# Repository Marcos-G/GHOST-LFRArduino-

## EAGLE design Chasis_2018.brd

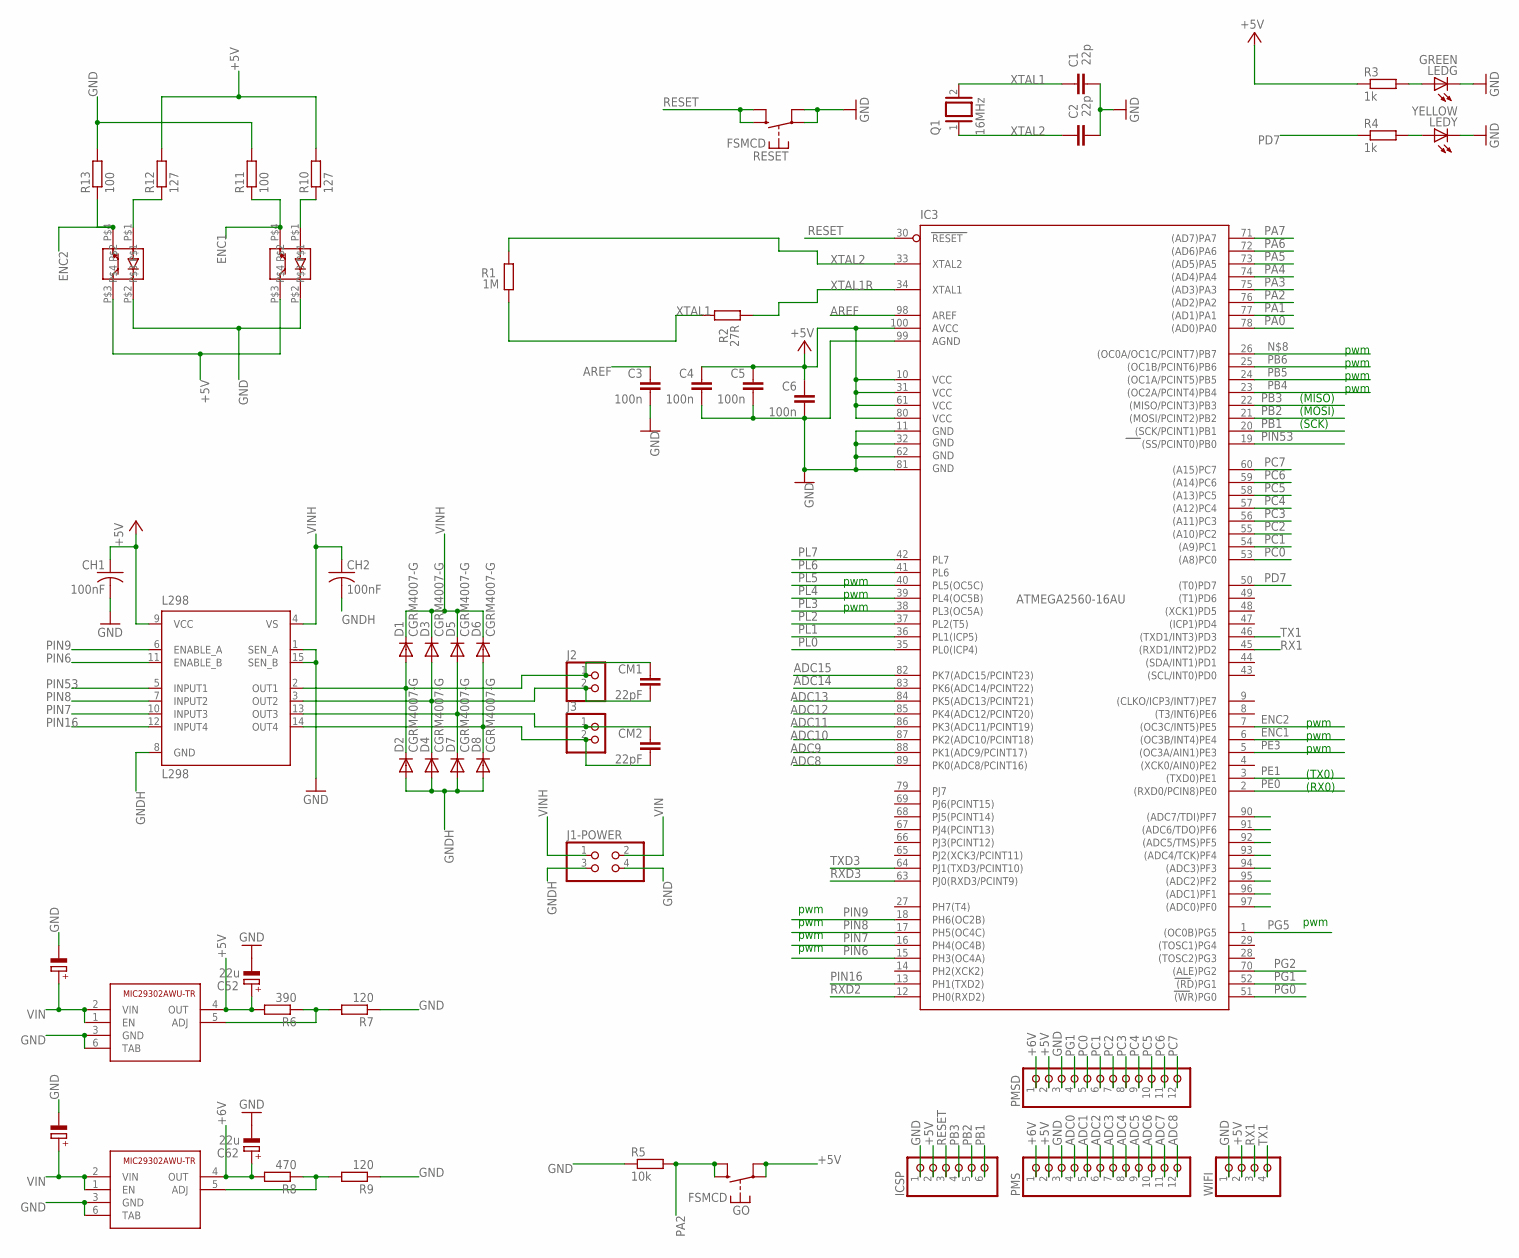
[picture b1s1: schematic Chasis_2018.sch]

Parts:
C1, C2: 22p; C0805K
C3, C4, C5, C6: 100n; C0805K
C51, C61: 10u; PANASONIC_D
C52, C62: 22u; PANASONIC_D
CH1, CH2: 100nF; C0805K
CM1, CM2: 22pF; C1206K
D1, D2, D3, D4, D5, D6, D7, D8: CGRM4007-G; SOD-123_MINI-SMA
ENC1, ENC2: EE-SX1046
GO: FSMCD
IC3: ATMEGA2560-16AU; TQFP100
ICSP: PINHD-1X6; 1X06
J1-POWER: PINHD-2X2; 2X02
J2, J3: PINHD-1X2; 1X02
L298: L298; MULTIWATT-15
LEDG: GREEN; CHIP-LED0805
LEDY: YELLOW; CHIP-LED0805
PMS: PINHD-1X12; 1X12
PMSD: PINHD-1X12; 1X12
Q1: 16MHz; QS
R1: 1M; R0805W
R2: 27R; R0805W
R3, R4: 1k; R0805W
R5: 10k; R0805W
R6: 390; R0805W
R7, R9: 120; R0805W
R8: 470; R0805W
R10, R12: 127; R0805W
R11, R13: 100; R0805W
REG5V, REG6V: MIC29302AWU-TR; TO263-5
RESET: FSMCD
WIFI: PINHD-1X4; 1X04

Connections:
+5V: C4.1, C5.1, C6.1, C52.+, CH1.1, ENC1.P$3, ENC2.P$3, GO.P$1, GO.P$2, IC3.10 (VCC), IC3.31 (VCC1), IC3.61 (VCC2), IC3.80 (VCC3), IC3.100 (AVCC), ICSP.2, L298.9 (VCC), PMS.2, PMSD.2, R3.1, R6.2, R10.2, R12.2, REG5V.4 (OUT), WIFI.2
+6V: C62.+, PMS.1, PMSD.1, R8.2, REG6V.4 (OUT)
ADC0: IC3.97 ((ADC0)PF0), PMS.4
ADC1: IC3.96 ((ADC1)PF1), PMS.5
ADC2: IC3.95 ((ADC2)PF2), PMS.6
ADC3: IC3.94 ((ADC3)PF3), PMS.7
ADC4: IC3.93 ((ADC4/TCK)PF4), PMS.8
ADC5: IC3.92 ((ADC5/TMS)PF5), PMS.9
ADC6: IC3.91 ((ADC6/TDO)PF6), PMS.10
ADC7: IC3.90 ((ADC7/TDI)PF7), PMS.11
ADC8: IC3.89 (PK0(ADC8/PCINT16)), PMS.12
ADC9: IC3.88 (PK1(ADC9/PCINT17))
ADC10: IC3.87 (PK2(ADC10/PCINT18))
ADC11: IC3.86 (PK3(ADC11/PCINT19))
ADC12: IC3.85 (PK4(ADC12/PCINT20))
ADC13: IC3.84 (PK5(ADC13/PCINT21))
ADC14: IC3.83 (PK6(ADC14/PCINT22))
ADC15: IC3.82 (PK7(ADC15/PCINT23))
AREF: C3.1, IC3.98 (AREF)
ENC1: ENC2.P$4, IC3.6 ((OC3B/INT4)PE4), R11.1
ENC2: ENC1.P$4, IC3.7 ((OC3C/INT5)PE5), R13.1
GND: C1.1, C2.1, C3.2, C4.2, C5.2, C6.2, C51.-, C52.-, C61.-, C62.-, CH1.2, ENC1.P$2, ENC2.P$2, IC3.11 (GND), IC3.32 (GND1), IC3.62 (GND2), IC3.81 (GND3), IC3.99 (AGND), ICSP.1, J1-POWER.4, L298.1 (SEN_A), L298.15 (SEN_B), LEDG.C, LEDY.C, PMS.3, PMSD.3, R5.1, R7.1, R9.1, R11.2, R13.2, REG5V.3 (GND), REG5V.6 (TAB), REG6V.3 (GND), REG6V.6 (TAB), RESET.P$1, RESET.P$2, WIFI.1
GNDH: CH2.2, D2.A, D4.A, D7.A, D8.A, J1-POWER.3, L298.8 (GND)
unnamed: CM1.1, D1.A, D2.C, J2.1, L298.2 (OUT1)
unnamed: LEDY.A, R4.2
unnamed: LEDG.A, R3.2
unnamed: CM1.2, D3.A, D4.C, J2.2, L298.3 (OUT2)
unnamed: CM2.2, D6.A, D8.C, J3.2, L298.14 (OUT4)
unnamed: CM2.1, D5.A, D7.C, J3.1, L298.13 (OUT3)
unnamed: ENC1.P$1, R12.1
unnamed: ENC2.P$1, R10.1
unnamed: R6.1, R7.2, REG5V.5 (ADJ)
unnamed: R8.1, R9.2, REG6V.5 (ADJ)
PA0: IC3.78 ((AD0)PA0)
PA1: IC3.77 ((AD1)PA1)
PA2: GO.P$3 (S), GO.P$4 (S), IC3.76 ((AD2)PA2), R5.2
PA3: IC3.75 ((AD3)PA3)
PA4: IC3.74 ((AD4)PA4)
PA5: IC3.73 ((AD5)PA5)
PA6: IC3.72 ((AD6)PA6)
PA7: IC3.71 ((AD7)PA7)
PB1: IC3.20 ((SCK/PCINT1)PB1), ICSP.6
PB2: IC3.21 ((MOSI/PCINT2)PB2), ICSP.5
PB3: IC3.22 ((MISO/PCINT3)PB3), ICSP.4
PB4: IC3.23 ((OC2A/PCINT4)PB4)
PB5: IC3.24 ((OC1A/PCINT5)PB5)
PB6: IC3.25 ((OC1B/PCINT6)PB6)
PC0: IC3.53 ((A8)PC0), PMSD.5
PC1: IC3.54 ((A9)PC1), PMSD.6
PC2: IC3.55 ((A10)PC2), PMSD.7
PC3: IC3.56 ((A11)PC3), PMSD.8
PC4: IC3.57 ((A12)PC4), PMSD.9
PC5: IC3.58 ((A13)PC5), PMSD.10
PC6: IC3.59 ((A14)PC6), PMSD.11
PC7: IC3.60 ((A15)PC7), PMSD.12
PD7: IC3.50 ((T0)PD7), R4.1
PE0: IC3.2 ((RXD0/PCIN8)PE0)
PE1: IC3.3 ((TXD0)PE1)
PE3: IC3.5 ((OC3A/AIN1)PE3)
PG0: IC3.51 ((WR)PG0)
PG1: IC3.52 ((RD)PG1), PMSD.4
PG2: IC3.70 ((ALE)PG2)
PG5: IC3.1 ((OC0B)PG5)
PIN6: IC3.15 (PH3(OC4A)), L298.11 (ENABLE_B)
PIN7: IC3.16 (PH4(OC4B)), L298.10 (INPUT3)
PIN8: IC3.17 (PH5(OC4C)), L298.7 (INPUT2)
PIN9: IC3.18 (PH6(OC2B)), L298.6 (ENABLE_A)
PIN16: IC3.13 (PH1(TXD2)), L298.12 (INPUT4)
PIN53: IC3.19 ((SS/PCINT0)PB0), L298.5 (INPUT1)
PL0: IC3.35 (PL0(ICP4))
PL1: IC3.36 (PL1(ICP5))
PL2: IC3.37 (PL2(T5))
PL3: IC3.38 (PL3(OC5A))
PL4: IC3.39 (PL4(OC5B))
PL5: IC3.40 (PL5(OC5C))
PL6: IC3.41 (PL6)
PL7: IC3.42 (PL7)
RESET: IC3.30 (RESET), ICSP.3, RESET.P$3 (S), RESET.P$4 (S)
RX1: IC3.45 ((RXD1/INT2)PD2), WIFI.3
RXD2: IC3.12 (PH0(RXD2))
RXD3: IC3.63 (PJ0(RXD3/PCINT9))
TX1: IC3.46 ((TXD1/INT3)PD3), WIFI.4
TXD3: IC3.64 (PJ1(TXD3/PCINT10))
VIN: C51.+, C61.+, J1-POWER.2, REG5V.1 (EN), REG5V.2 (VIN), REG6V.1 (EN), REG6V.2 (VIN)
VINH: CH2.1, D1.C, D3.C, D5.C, D6.C, J1-POWER.1, L298.4 (VS)
XTAL1: C1.2, Q1.2, R1.1, R2.2
XTAL1R: IC3.34 (XTAL1), R2.1
XTAL2: C2.2, IC3.33 (XTAL2), Q1.1, R1.2

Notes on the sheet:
pwm
(TX0)
(RX0)
(MISO)
(SCK)
(MOSI)

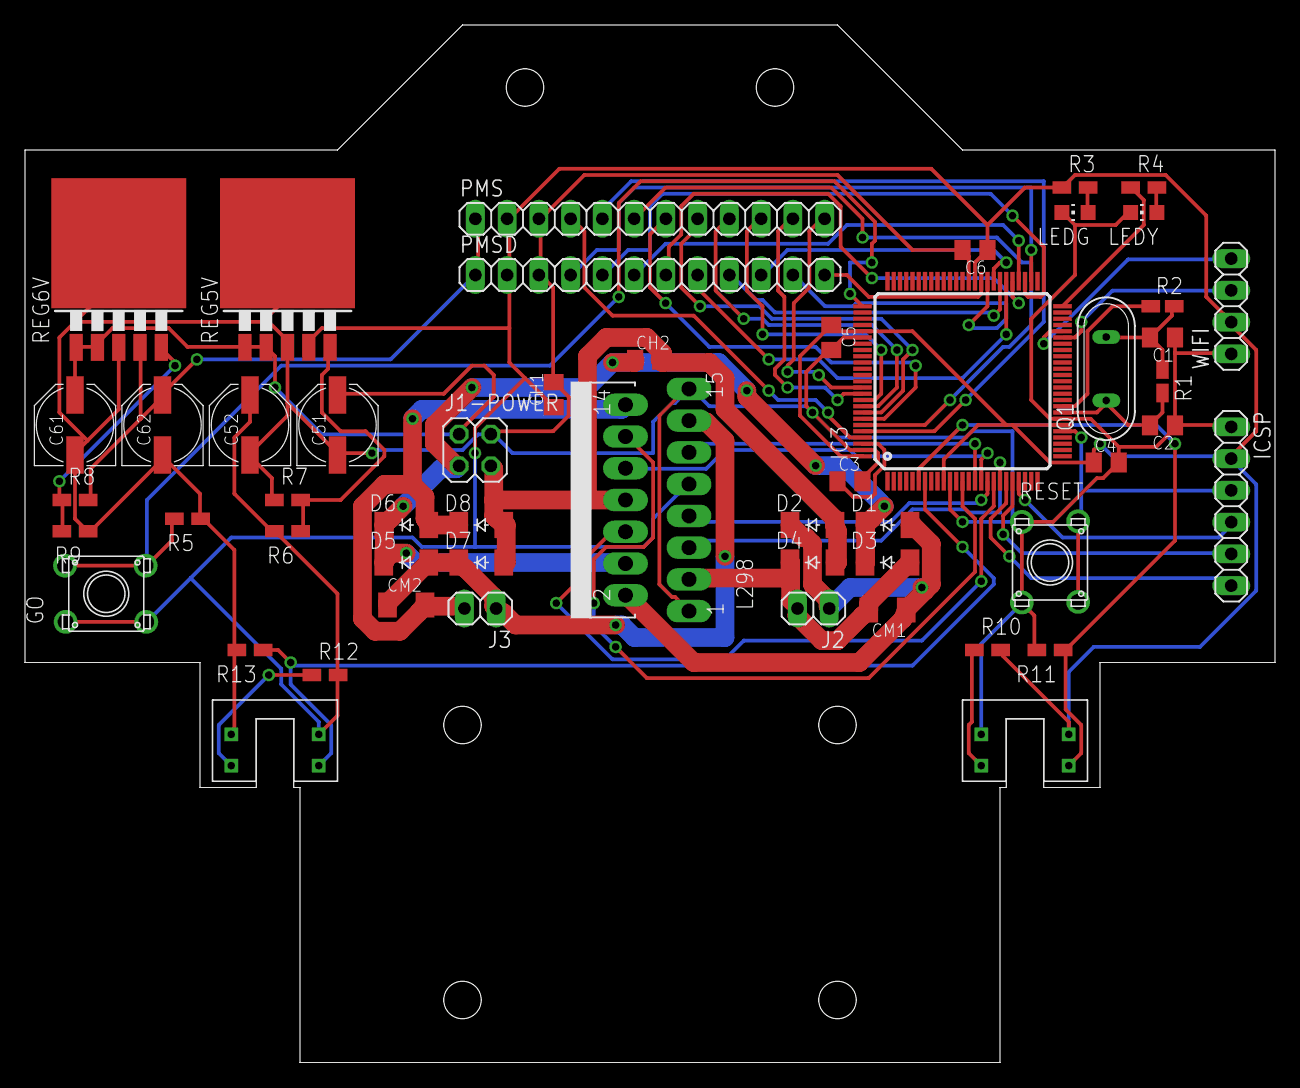
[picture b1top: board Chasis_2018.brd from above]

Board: 2 copper layers, 100.0 x 83.0 mm, 53 parts (0 on the bottom side), 54 nets.

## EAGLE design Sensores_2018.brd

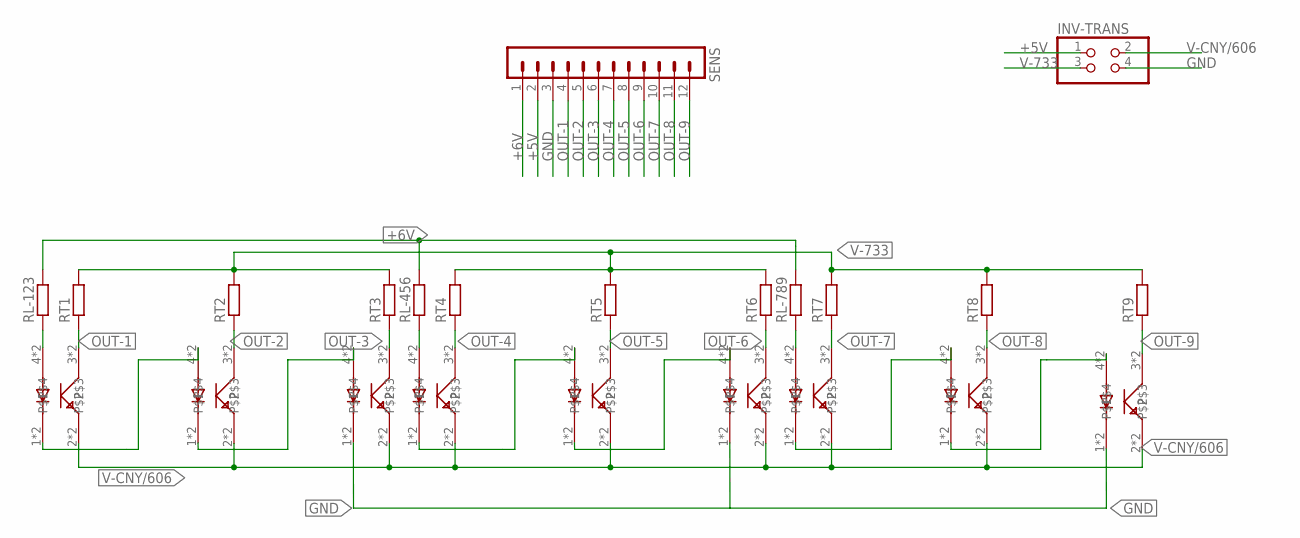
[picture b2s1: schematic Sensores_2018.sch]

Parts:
INV-TRANS: PINHD-2X2; 2X02
RL-123, RL-456, RL-789: R-EU_R0805W; R0805W
RT1, RT2, RT3, RT4, RT5, RT6, RT7, RT8, RT9: R-EU_R0805W; R0805W
S1, S2, S3, S4, S5, S6, S7, S8, S9: OPB733+OPB606+CNY70; OPB733+606
SENS: MA12-1

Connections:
+5V: INV-TRANS.1, SENS.2
+6V: RL-123.2, RL-456.2, RL-789.2, SENS.1
GND: INV-TRANS.4, S3.1, S3.P$1, S6.1, S6.P$1, S9.1, S9.P$1, SENS.3
unnamed: RL-123.1, S1.4, S1.P$4
unnamed: S1.1, S1.P$1, S2.4, S2.P$4
unnamed: S2.1, S2.P$1, S3.4, S3.P$4
unnamed: RL-456.1, S4.4, S4.P$4
unnamed: S4.1, S4.P$1, S5.4, S5.P$4
unnamed: S5.1, S5.P$1, S6.4, S6.P$4
unnamed: RL-789.1, S7.4, S7.P$4
unnamed: S7.1, S7.P$1, S8.4, S8.P$4
unnamed: S8.1, S8.P$1, S9.4, S9.P$4
OUT-1: RT1.1, S1.3, S1.P$3, SENS.4
OUT-2: RT2.1, S2.3, S2.P$3, SENS.5
OUT-3: RT3.1, S3.3, S3.P$3, SENS.6
OUT-4: RT4.1, S4.3, S4.P$3, SENS.7
OUT-5: RT5.1, S5.3, S5.P$3, SENS.8
OUT-6: RT6.1, S6.3, S6.P$3, SENS.9
OUT-7: RT7.1, S7.3, S7.P$3, SENS.10
OUT-8: RT8.1, S8.3, S8.P$3, SENS.11
OUT-9: RT9.1, S9.3, S9.P$3, SENS.12
V-733: INV-TRANS.3, RT1.2, RT2.2, RT3.2, RT4.2, RT5.2, RT6.2, RT7.2, RT8.2, RT9.2
V-CNY/606: INV-TRANS.2, S1.2, S1.P$2, S2.2, S2.P$2, S3.2, S3.P$2, S4.2, S4.P$2, S5.2, S5.P$2, S6.2, S6.P$2, S7.2, S7.P$2, S8.2, S8.P$2, S9.2, S9.P$2

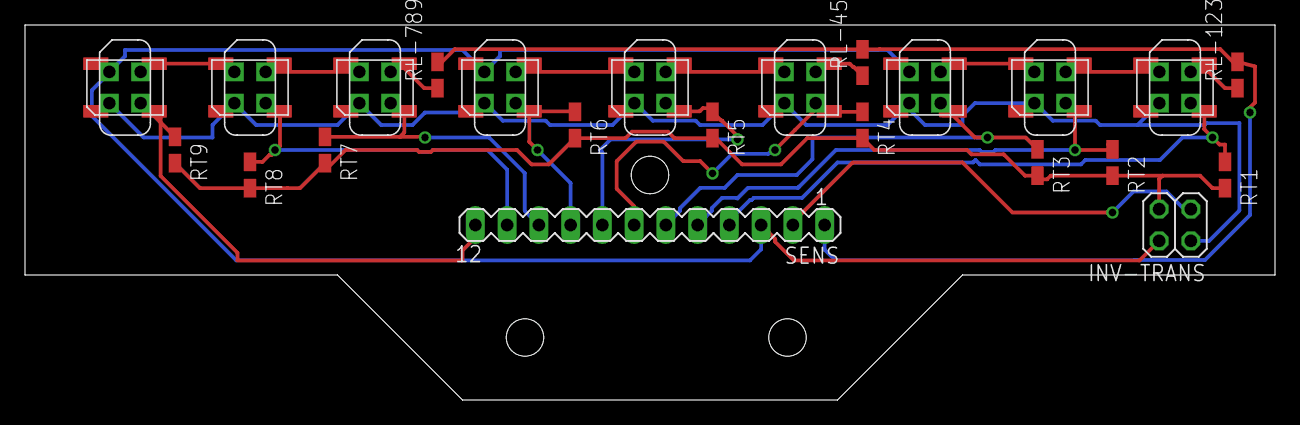
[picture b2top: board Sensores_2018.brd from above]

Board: 2 copper layers, 100.0 x 30.0 mm, 23 parts (0 on the bottom side), 23 nets.

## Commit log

2018-07-31 files added
2018-07-31 auto commit
